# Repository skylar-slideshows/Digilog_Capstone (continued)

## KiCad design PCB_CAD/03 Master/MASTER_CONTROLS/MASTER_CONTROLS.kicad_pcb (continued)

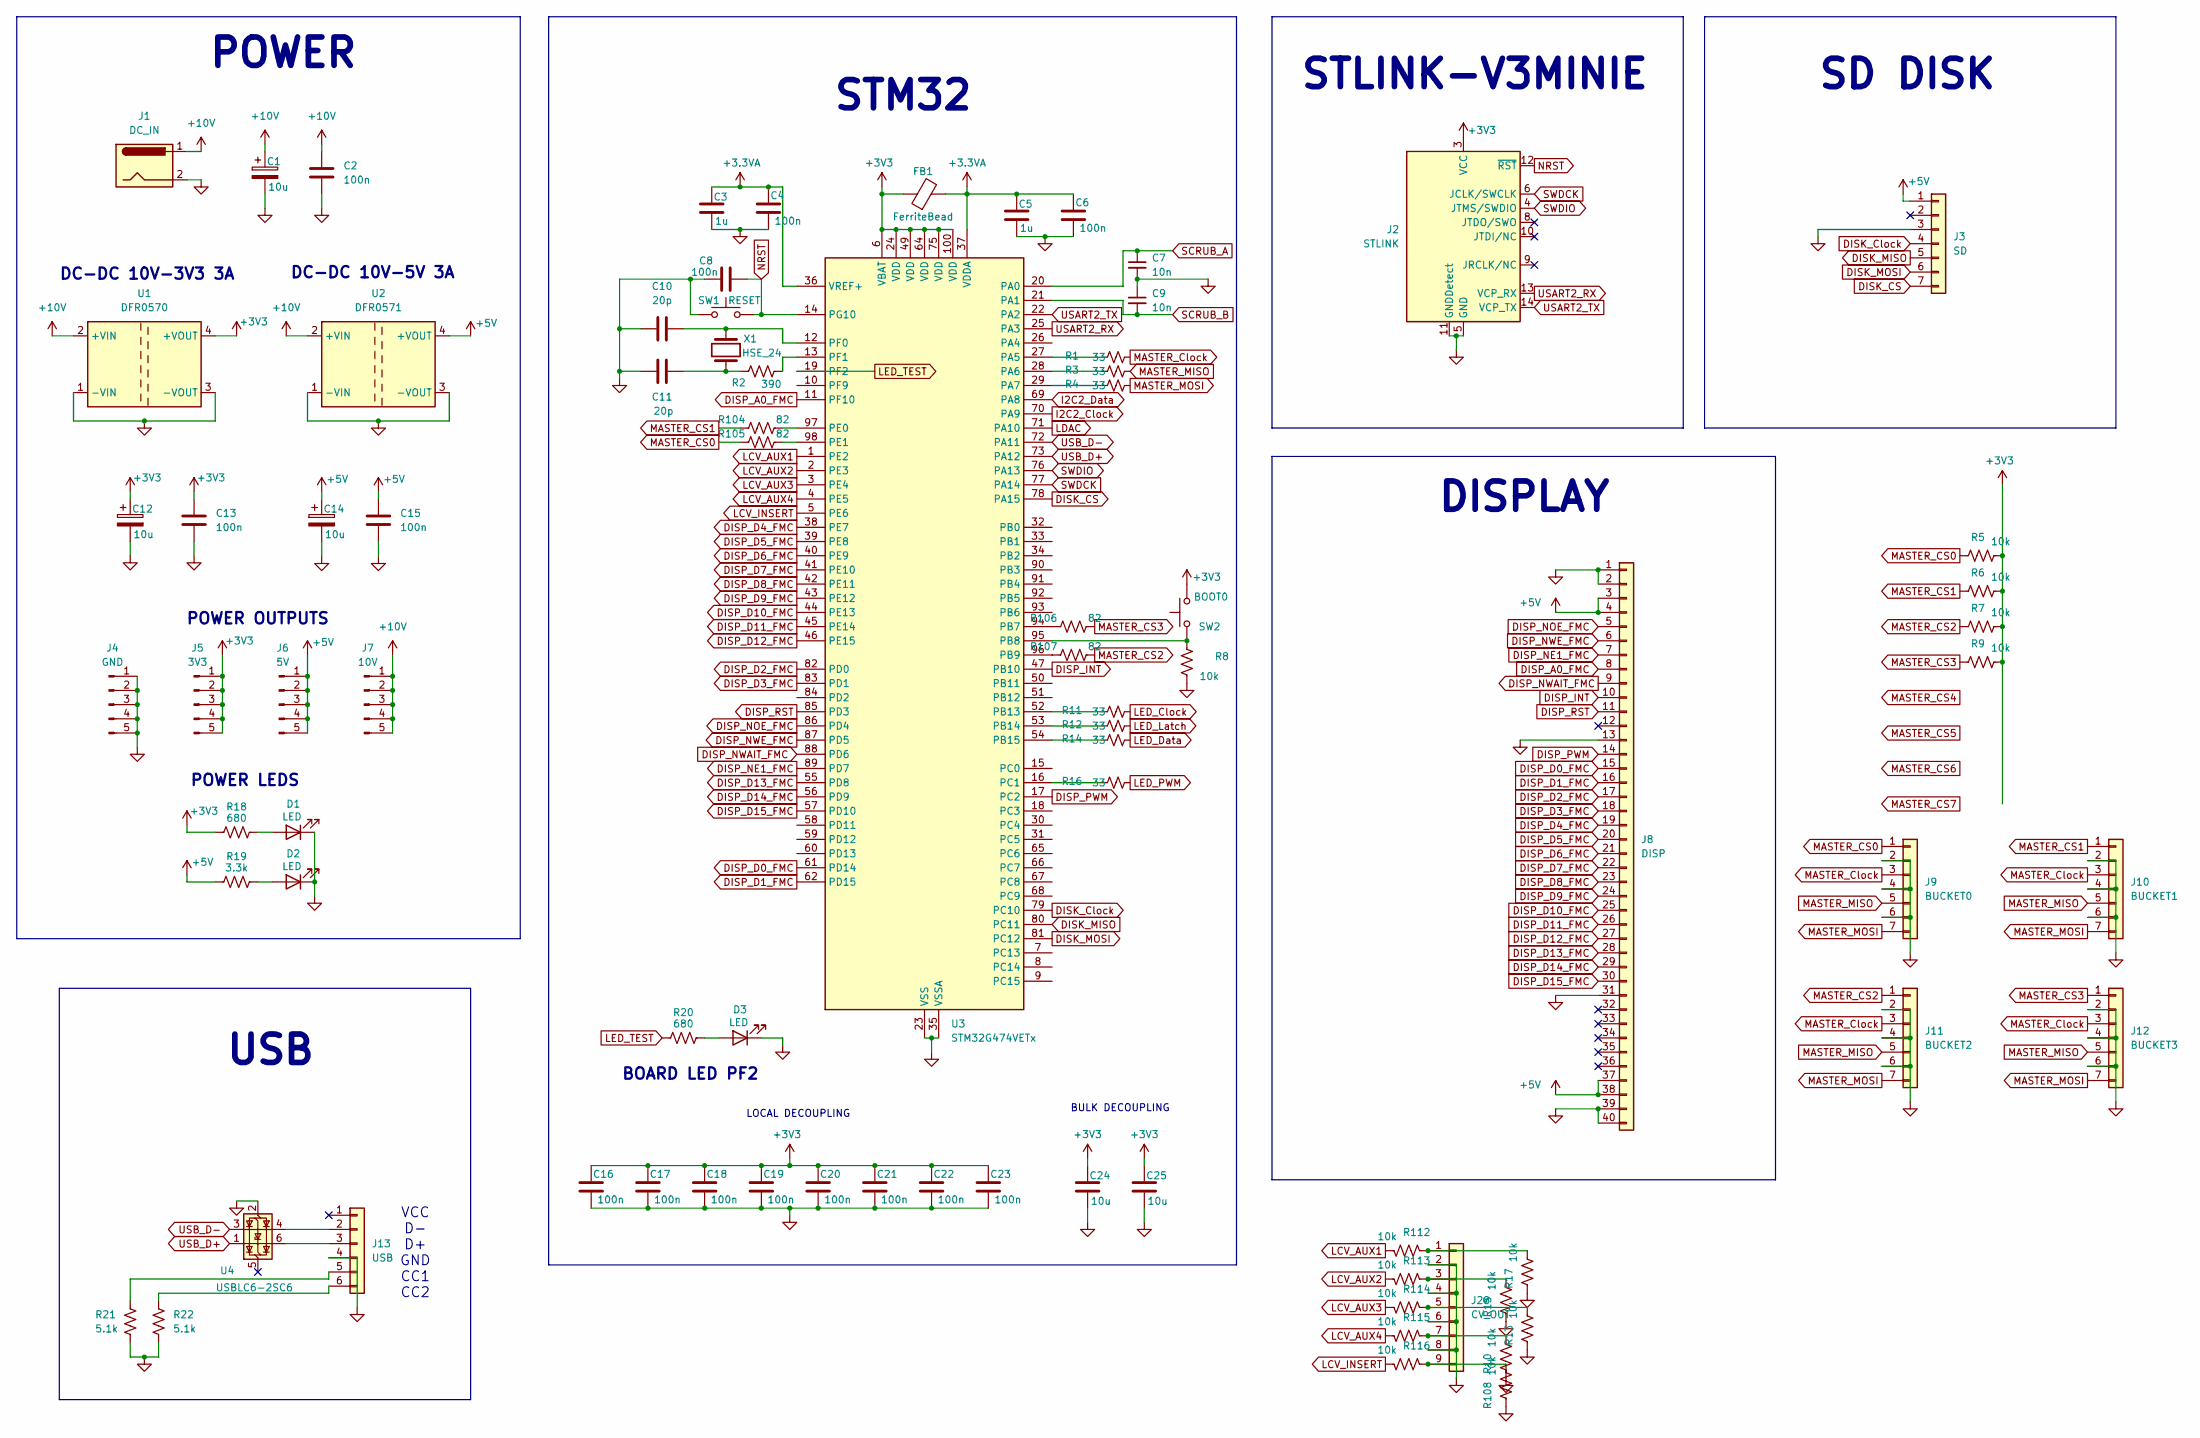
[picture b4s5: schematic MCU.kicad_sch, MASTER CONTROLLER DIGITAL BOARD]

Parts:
C1, C12, C14, C24, C25: 10u; C_1206_3216Metric; LCSC C1849
C2, C4, C6, C8, C13, C15, C16, C17, C18, C19, C20, C21, C22, C23: 100n; C_0603_1608Metric; LCSC C1590
C3, C5: 1u; C_0603_1608Metric; LCSC C15849
C7, C9: 10n; C_0402_1005Metric; LCSC C1524
C10, C11: 20p; C_0603_1608Metric; LCSC C1648
D1, D2, D3: LED; LED_0603_1608Metric; LCSC C12065
FB1: FerriteBead; Ferrite_0603_1608Metric; LCSC C1002
J1: DC_IN; BarrelJack_Horizontal; LCSC DNP
J2: STLINK; FTSH-107-01-L-DV-K-TR; LCSC C5307809
J3: SD; PinHeader_1x07_P2.54mm_Vertical; LCSC DNP
J4: GND; PinSocket_1x05_P2.54mm_Vertical; LCSC DNP
J5: 3V3; PinSocket_1x05_P2.54mm_Vertical; LCSC DNP
J6: 5V; PinSocket_1x05_P2.54mm_Vertical; LCSC DNP
J7: 10V; PinSocket_1x05_P2.54mm_Vertical; LCSC DNP
J8: DISP; GCT_FFC3B07-40-T; LCSC DNP
J9: BUCKET0; PinHeader_1x07_P2.54mm_Vertical; LCSC DNP
J10: BUCKET1; PinHeader_1x07_P2.54mm_Vertical; LCSC DNP
J11: BUCKET2; PinHeader_1x07_P2.54mm_Vertical; LCSC DNP
J12: BUCKET3; PinHeader_1x07_P2.54mm_Vertical; LCSC DNP
J13: USB; PinHeader_1x06_P2.00mm_Vertical; Part Number 1-0601FBV0T; LCSC dnp
J28: CV_OUT; PinHeader_1x09_P2.54mm_Vertical; LCSC DNP
R1, R3, R4, R11, R12, R14, R16: 33; R_0603_1608Metric; LCSC C23140
R2: 390; R_1206_3216Metric; LCSC C4491
R5, R6, R7, R8, R9, R10, R13, R15, R17, R108: 10k; R_0603_1608Metric; LCSC C25804
R18, R20: 680; R_0603_1608Metric; LCSC C23228
R19: 3.3k; R_0603_1608Metric; LCSC C22978
R21, R22: 5.1k; R_0603_1608Metric; LCSC C14677
R104, R105, R106, R107: 82; R_0603_1608Metric; LCSC C23255
R112, R113, R114, R115, R116: 10k; R_0603_1608Metric; LCSC C21190
SW1: RESET; SW_Push_1P1T_NO_CK_KMR2; LCSC C72443
SW2: BOOT0; SW_Push_1P1T_NO_CK_KMR2; LCSC C72443
U1: DFR0570; DFR05xx_DC-DC; LCSC DNP
U2: DFR0571; DFR05xx_DC-DC; LCSC DNP
U3: STM32G474VETx; LQFP-100_14x14mm_P0.5mm; LCSC C2970837
U4: USBLC6-2SC6; SOT-23-6; LCSC C7519
X1: HSE_24; Crystal_SMD_HC49-SD; LCSC C2253

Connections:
+3.3VA: C3.1, C4.1, C5.1, C6.1, FB1.2, U3.36 (VREF+), U3.37 (VDDA)
+3V3: C12.1, C13.1, C16.1, C17.1, C18.1, C19.1, C20.1, C21.1, C22.1, C23.1, C24.1, C25.1, FB1.1, J2.3 (VCC), J5.1, J5.2, J5.3, J5.4, J5.5, R5.2, R6.2, R7.2, R9.2, R18.1, SW2.2, U1.4 (+VOUT), U3.6 (VBAT), U3.24 (VDD), U3.49 (VDD), U3.64 (VDD), U3.75 (VDD), U3.100 (VDD); also elsewhere on the board
+5V: C14.1, C15.1, J3.1, J6.1, J6.2, J6.3, J6.4, J6.5, J8.3, J8.4, J8.37, J8.38, R19.1, U2.4 (+VOUT); also elsewhere on the board
+10V: C1.1, C2.1, J1.1, J7.1, J7.2, J7.3, J7.4, J7.5, U1.2 (+VIN), U2.2 (+VIN)
DISK_CS: J3.7, U3.78 (PA15)
DISK_Clock: J3.4, U3.79 (PC10)
DISK_MISO: J3.5, U3.80 (PC11)
DISK_MOSI: J3.6, U3.81 (PC12)
DISP_A0_FMC: J8.8, U3.11 (PF10)
DISP_D0_FMC: J8.15, U3.61 (PD14)
DISP_D1_FMC: J8.16, U3.62 (PD15)
DISP_D2_FMC: J8.17, U3.82 (PD0)
DISP_D3_FMC: J8.18, U3.83 (PD1)
DISP_D4_FMC: J8.19, U3.38 (PE7)
DISP_D5_FMC: J8.20, U3.39 (PE8)
DISP_D6_FMC: J8.21, U3.40 (PE9)
DISP_D7_FMC: J8.22, U3.41 (PE10)
DISP_D8_FMC: J8.23, U3.42 (PE11)
DISP_D9_FMC: J8.24, U3.43 (PE12)
DISP_D10_FMC: J8.25, U3.44 (PE13)
DISP_D11_FMC: J8.26, U3.45 (PE14)
DISP_D12_FMC: J8.27, U3.46 (PE15)
DISP_D13_FMC: J8.28, U3.55 (PD8)
DISP_D14_FMC: J8.29, U3.56 (PD9)
DISP_D15_FMC: J8.30, U3.57 (PD10)
DISP_INT: J8.10, U3.47 (PB10)
DISP_NE1_FMC: J8.7, U3.89 (PD7)
DISP_NOE_FMC: J8.5, U3.86 (PD4)
DISP_NWAIT_FMC: J8.9, U3.88 (PD6)
DISP_NWE_FMC: J8.6, U3.87 (PD5)
DISP_PWM: J8.14, U3.17 (PC2)
DISP_RST: J8.11, U3.85 (PD3)
GND: C1.2, C2.2, C3.2, C4.2, C5.2, C6.2, C7.2, C8.1, C9.1, C10.2, C11.1, C12.2, C13.2, C14.2, C15.2, C16.2, C17.2, C18.2, C19.2, C20.2, C21.2, C22.2, C23.2, C24.2, C25.2, D1.1 (K), D2.1 (K), D3.1 (K), J1.2, J2.5 (GND), J2.7 (GND), J2.11 (GNDDetect), J3.3, J4.1, J4.2, J4.3, J4.4, J4.5, J8.1, J8.2, J8.13, J8.31, J8.39, J8.40, J9.2, J9.4, J9.6, J10.2, J10.4, J10.6, J11.2, J11.4, J11.6, J12.2, J12.4, J12.6, J13.4, J28.2, J28.4, J28.6, J28.8, R8.1, R10.1, R13.1, R15.1, R17.1, R21.1, R22.1, R108.1, SW1.1, U1.1 (-VIN), U1.3 (-VOUT), U2.1 (-VIN), U2.3 (-VOUT), U3.23 (VSS), U3.35 (VSSA), U3.48 (VSS), U3.63 (VSS), U3.74 (VSS), U3.99 (VSS), U4.2 (GND); also elsewhere on the board
I2C2_Clock: U3.70 (PA9); also elsewhere on the board
I2C2_Data: U3.69 (PA8); also elsewhere on the board
LCV_AUX1: R112.2, U3.1 (PE2)
LCV_AUX2: R113.2, U3.2 (PE3)
LCV_AUX3: R114.2, U3.3 (PE4)
LCV_AUX4: R115.2, U3.4 (PE5)
LCV_INSERT: R116.2, U3.5 (PE6)
LDAC: U3.71 (PA10); also elsewhere on the board
LED_Clock: R11.2; also elsewhere on the board
LED_Data: R14.2; also elsewhere on the board
LED_Latch: R12.2; also elsewhere on the board
LED_PWM: R16.2; also elsewhere on the board
LED_TEST: R20.1, U3.19 (PF2)
MASTER_CS0: J9.1, R5.1, R105.1
MASTER_CS1: J10.1, R6.1, R104.1
MASTER_CS2: J11.1, R7.1, R107.2
MASTER_CS3: J12.1, R9.1, R106.2
MASTER_Clock: J9.3, J10.3, J11.3, J12.3, R1.2
MASTER_MISO: J9.5, J10.5, J11.5, J12.5, R3.2
MASTER_MOSI: J9.7, J10.7, J11.7, J12.7, R4.2
NRST: C8.2, J2.12 (~RST), SW1.2, U3.14 (PG10)
unnamed: C11.2, R2.1, X1.2
unnamed: D1.2 (A), R18.2
unnamed: D2.2 (A), R19.2
unnamed: D3.2 (A), R20.2
unnamed: J13.2, U4.4 (I/O2)
unnamed: J13.3, U4.6 (I/O1)
unnamed: J13.5, R21.2
unnamed: J13.6, R22.2
unnamed: J28.1, R17.2, R112.1
unnamed: J28.3, R15.2, R113.1
unnamed: J28.5, R13.2, R114.1
unnamed: J28.7, R10.2, R115.1
unnamed: J28.9, R108.2, R116.1
unnamed: R1.1, U3.27 (PA5)
unnamed: R3.1, U3.28 (PA6)
unnamed: R4.1, U3.29 (PA7)
unnamed: R106.1, U3.94 (PB7)
unnamed: R8.2, SW2.1, U3.95 (PB8)
unnamed: R107.1, U3.96 (PB9)
unnamed: R11.1, U3.52 (PB13)
unnamed: R12.1, U3.53 (PB14)
unnamed: R14.1, U3.54 (PB15)
unnamed: R16.1, U3.16 (PC1)
unnamed: R104.2, U3.97 (PE0)
unnamed: R105.2, U3.98 (PE1)
unnamed: C10.1, U3.12 (PF0), X1.1
unnamed: R2.2, U3.13 (PF1)
SCRUB_A: C7.1, U3.20 (PA0); also elsewhere on the board
SCRUB_B: C9.2, U3.21 (PA1); also elsewhere on the board
SWDCK: J2.6 (JCLK/SWCLK), U3.77 (PA14)
SWDIO: J2.4 (JTMS/SWDIO), U3.76 (PA13)
USART2_RX: J2.13 (VCP_RX), U3.25 (PA3)
USART2_TX: J2.14 (VCP_TX), U3.22 (PA2)
USB_D+: U3.73 (PA12), U4.1 (I/O1)
USB_D-: U3.72 (PA11), U4.3 (I/O2)

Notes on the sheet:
DISPLAY
POWER LEDS
STLINK-V3MINIE
STM32
DC-DC 10V-5V 3A
BULK DECOUPLING
LOCAL DECOUPLING
POWER
BOARD LED PF2
POWER OUTPUTS
DC-DC 10V-3V3 3A
SD DISK
USB
VCC D- D+ GND CC1 CC2

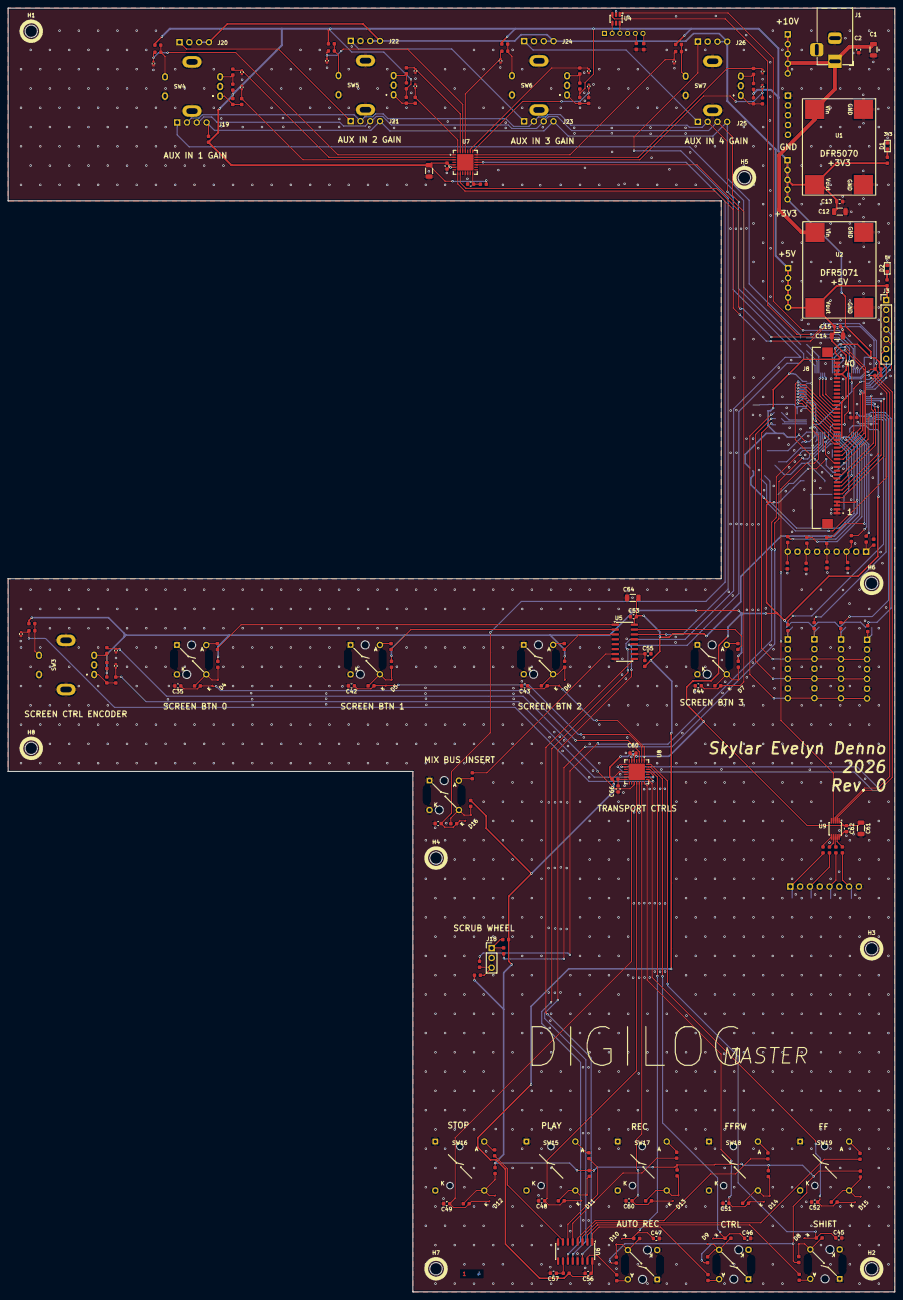
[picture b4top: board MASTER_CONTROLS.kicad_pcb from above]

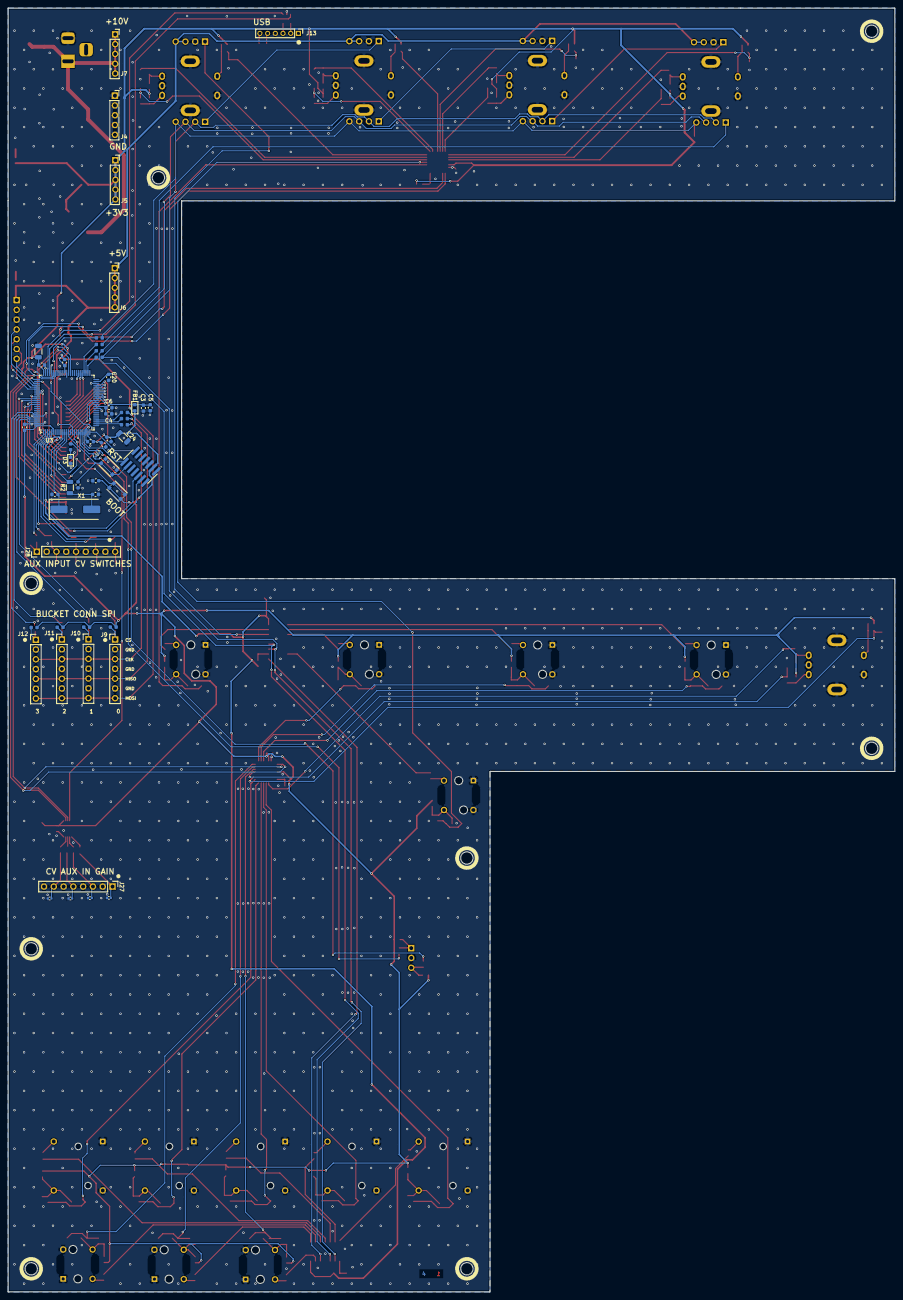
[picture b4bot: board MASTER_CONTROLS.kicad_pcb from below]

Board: 4 copper layers, 230.0 x 333.0 mm, 264 parts (54 on the bottom side), 190 nets.

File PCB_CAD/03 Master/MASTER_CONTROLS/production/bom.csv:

Designator,Footprint,Quantity,Value,LCSC Part #
"C1, C12, C14, C24, C25, C54, C59, C61",1206,8,10u,C1849
"C10, C11",0603,2,20p,C1648
"C13, C15, C16, C17, C18, C19, C2, C20, C21, C22, C23, C4, C53, C55, C56, C57, C58, C6, C60, C62, C65, C66, C8",0603,23,100n,C1590
"C26, C27, C28, C29, C30, C31, C32, C33, C34, C36, C37, C38, C39, C40, C41, C63, C64, C67, C68, C7, C9",0402,21,10n,C1524
"C3, C35, C42, C43, C44, C45, C46, C47, C48, C49, C5, C50, C51, C52, C69",0603,15,1u,C15849
"D1, D2, D3",0603,3,LED,C12065
"D10, D11, D12, D13, D14, D15, D16, D4, D5, D6, D7, D8, D9",D_SOD-323,13,1N4148,C2128
FB1,Ferrite_0603_1608Metric,1,FerriteBead,C1002
J1,BarrelJack_Horizontal,1,DC_IN,DNP
J10,PinHeader_1x07_P2.54mm_Vertical,1,BUCKET1,DNP
J11,PinHeader_1x07_P2.54mm_Vertical,1,BUCKET2,DNP
J12,PinHeader_1x07_P2.54mm_Vertical,1,BUCKET3,DNP
J13,PinHeader_1x06_P2.00mm_Vertical,1,USB,dnp
J18,PinHeader_1x03_P2.54mm_Vertical,1,SCRUB_ENCODER,DNP
"J19, J21, J23, J25",PinSocket_1x04_P2.54mm_Vertical,4,Data,DNP
J2,FTSH-107-01-L-DV-K-TR,1,STLINK,C5307809
"J20, J22, J24, J26",PinSocket_1x04_P2.54mm_Vertical,4,Pow,DNP
J27,PinHeader_1x08_P2.54mm_Vertical,1,CV_OUT,DNP
J28,PinHeader_1x09_P2.54mm_Vertical,1,CV_OUT,DNP
J3,PinHeader_1x07_P2.54mm_Vertical,1,SD,DNP
J4,PinSocket_1x05_P2.54mm_Vertical,1,GND,DNP
J5,PinSocket_1x05_P2.54mm_Vertical,1,3V3,DNP
J6,PinSocket_1x05_P2.54mm_Vertical,1,5V,DNP
J7,PinSocket_1x05_P2.54mm_Vertical,1,10V,DNP
J8,GCT_FFC3B07-40-T,1,DISP,DNP
J9,PinHeader_1x07_P2.54mm_Vertical,1,BUCKET0,DNP
"R1, R11, R12, R14, R16, R3, R4",0603,7,33,C23140
"R10, R100, R108, R13, R15, R17, R23, R24, R25, R26, R27, R28, R29, R30, R31, R43, R44, R45, R46, R47, R48, R5, R6, R7, R75, R8, R81, R9, R93, R94, R95, R99",0603,32,10k,C25804
"R101, R102, R103, R96",0603,4,470,C23179
"R104, R105, R106, R107",0603,4,82,C23255
"R109, R41, R42, R59, R60, R63, R64, R65, R76, R77, R78, R79, R80",0603,13,47k,C25819
"R110, R57, R58, R66, R67, R71, R72, R73, R88, R89, R90, R91, R92",0603,13,470,C25241
"R111, R49, R52, R61, R62, R68, R69, R70, R74, R82, R83, R84, R85, R86, R87",0603,15,15k,C22809
"R112, R113, R114, R115, R116",0603,5,10k,C21190
"R18, R20",0603,2,680,C23228
R19,0603,1,3.3k,C22978
R2,1206,1,390,C4491
"R21, R22",0603,2,5.1k,C14677
"R32, R33, R34, R35, R36, R37, R38, R39, R40, R50, R51, R53, R54, R55, R56",0603,15,1k,C21190
"R97, R98",0603,2,1.5k,C22843
SW1,SW_Push_1P1T_NO_CK_KMR2,1,RESET,C72443
SW10,CFPB-1CC-4W6_LOWPROF,1,B2,DNP
SW11,CFPB-1CC-4W6_LOWPROF,1,B3,DNP
SW12,CFPB-1CC-4W6_LOWPROF,1,B4,DNP
"SW13, SW14",CFPB-1CC-4W6_LOWPROF,2,B5,DNP
SW15,CFPB-1CC-4W2,1,B_PLAY,DNP
SW16,CFPB-1CC-4W2,1,B_STOP,DNP
SW17,CFPB-1CC-4W2,1,B_REC,DNP
SW18,CFPB-1CC-4W2,1,B_FRW,DNP
SW19,CFPB-1CC-4W2,1,B_FF,DNP
SW2,SW_Push_1P1T_NO_CK_KMR2,1,BOOT0,C72443
SW20,CFPB-1CC-4W6_LOWPROF,1,INSERT,DNP
SW3,EC11J0924411,1,K4,DNP
SW4,EC11J0924411,1,K0,DNP
SW5,EC11J0924411,1,K1,DNP
SW6,EC11J0924411,1,K2,DNP
SW7,EC11J0924411,1,K3,DNP
SW8,CFPB-1CC-4W6_LOWPROF,1,B0,DNP
SW9,CFPB-1CC-4W6_LOWPROF,1,B1,DNP
U1,DFR05xx_DC-DC,1,DFR0570,DNP
U2,DFR05xx_DC-DC,1,DFR0571,DNP
U3,LQFP-100_14x14mm_P0.5mm,1,STM32G474VETx,C2970837
U4,SOT-23-6,1,USBLC6-2SC6,C7519
"U5, U6",SOIC-16_3.9x9.9mm_P1.27mm,2,74HCT595,C282339
U7,QFN-28-1EP_6x6mm_P0.65mm_EP4.25x4.25mm,1,MCP23017_0,C629439
U8,QFN-28-1EP_6x6mm_P0.65mm_EP4.25x4.25mm,1,MCP23017_1,C629439
U9,MSOP-10_3x3mm_P0.5mm,1,MCP4728,C108207
X1,Crystal_SMD_HC49-SD,1,HSE_24,C2253

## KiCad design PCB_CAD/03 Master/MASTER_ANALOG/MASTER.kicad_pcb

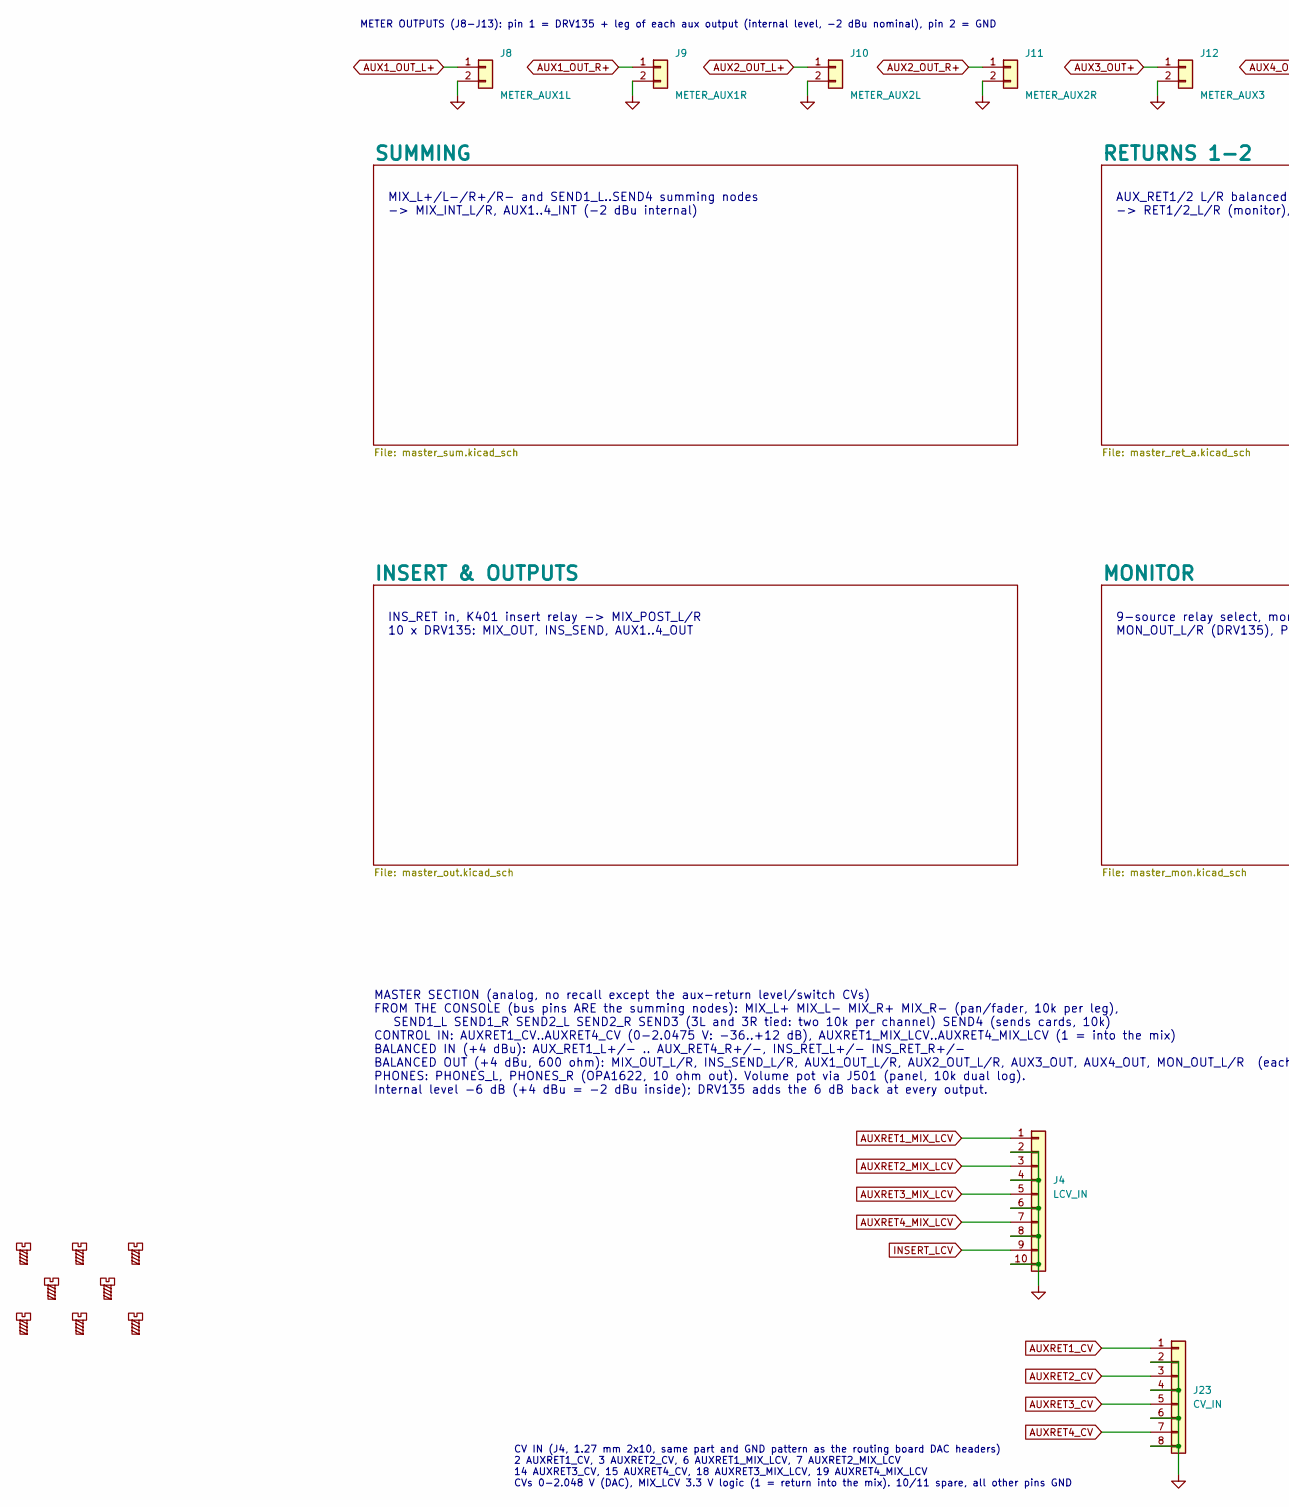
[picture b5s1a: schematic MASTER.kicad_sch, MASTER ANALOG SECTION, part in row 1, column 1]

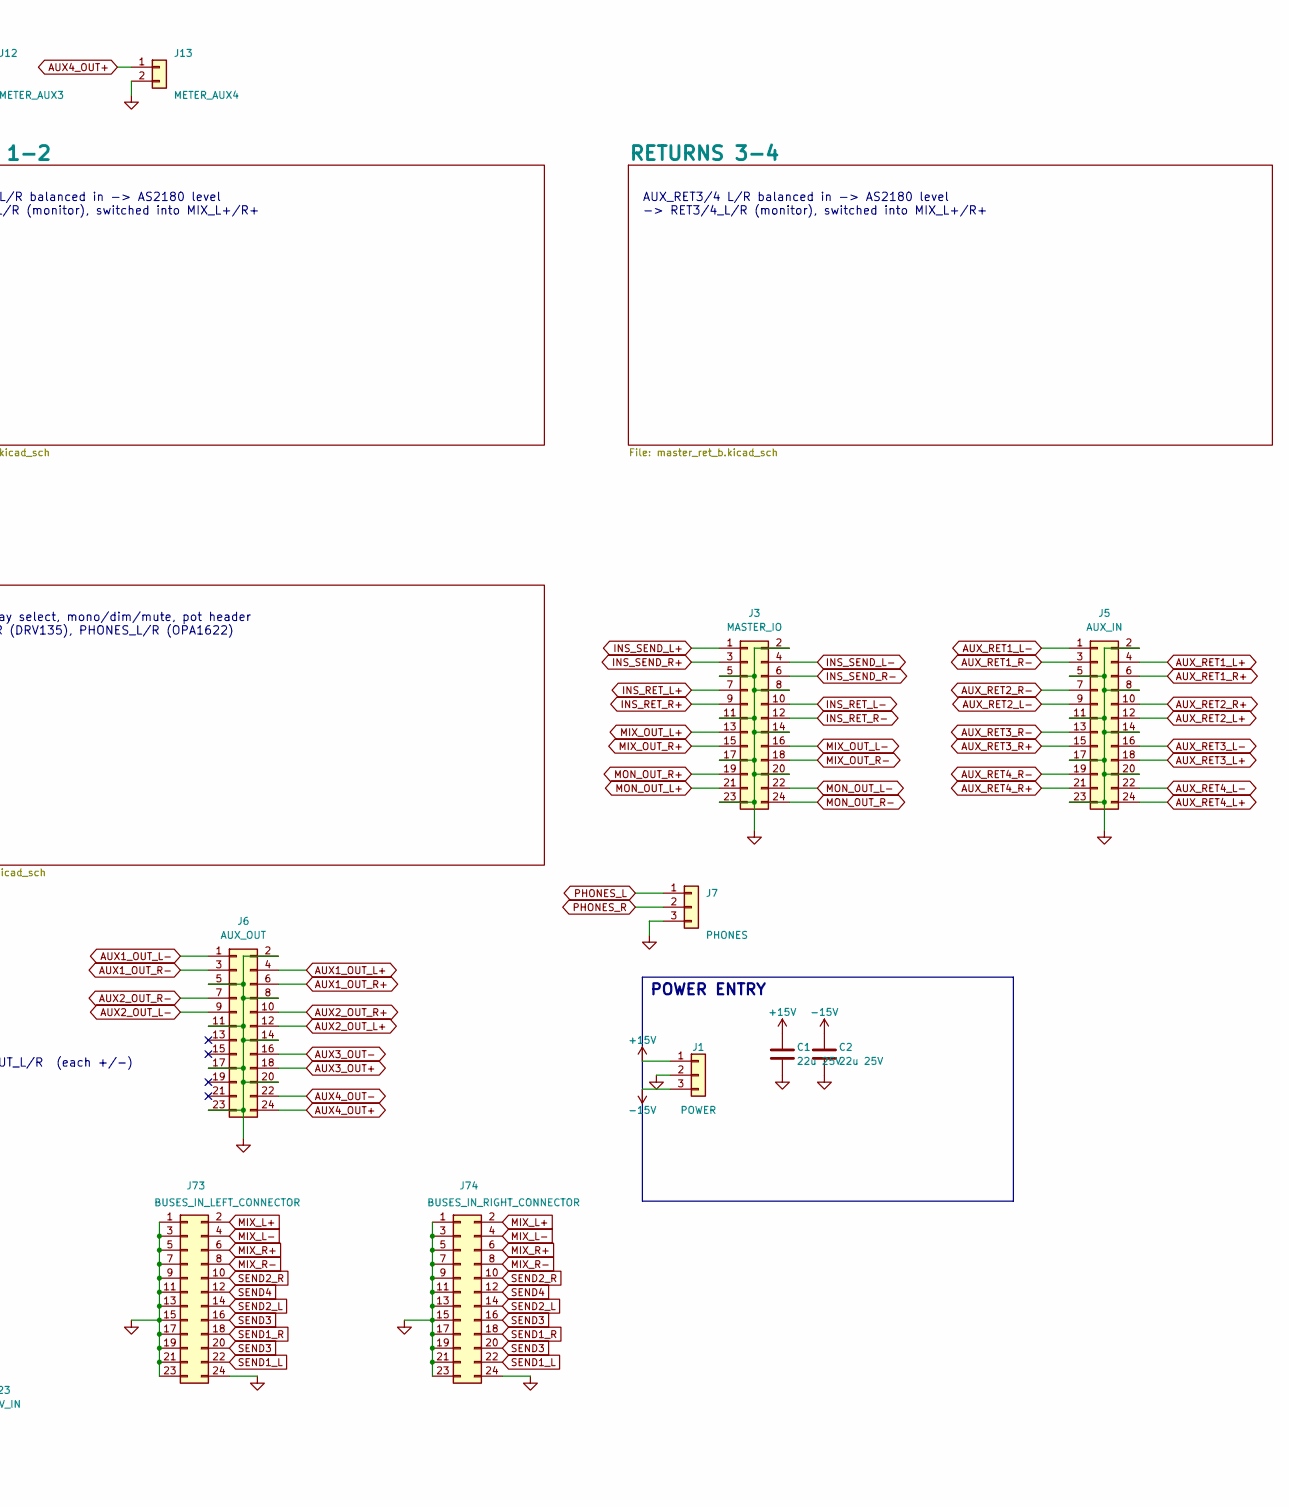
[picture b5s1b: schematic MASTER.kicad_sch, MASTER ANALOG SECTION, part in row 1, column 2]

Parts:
C1, C2: 22u 25V; C_1210_3225Metric; LCSC C21397
H1, H2, H3, H4, H5, H6, H7, H8: MountingScrew; MountingHole_3.2mm_M3; LCSC dnp
J1: POWER; Samtec_HPM-03-05-x-S_Straight_1x03_Pitch5.08mm; LCSC dnp
J3: MASTER_IO; IDC-Header_2x12_P2.54mm_Vertical; LCSC C53207829
J4: LCV_IN; PinHeader_1x10_P2.54mm_Vertical; LCSC dnp
J5: AUX_IN; IDC-Header_2x12_P2.54mm_Vertical; LCSC C53207829
J6: AUX_OUT; IDC-Header_2x12_P2.54mm_Vertical; LCSC C53207829
J7: PHONES; PinHeader_1x03_P2.54mm_Vertical; LCSC dnp
J8: METER_AUX1L; PinHeader_1x02_P2.54mm_Vertical; LCSC dnp
J9: METER_AUX1R; PinHeader_1x02_P2.54mm_Vertical; LCSC dnp
J10: METER_AUX2L; PinHeader_1x02_P2.54mm_Vertical; LCSC dnp
J11: METER_AUX2R; PinHeader_1x02_P2.54mm_Vertical; LCSC dnp
J12: METER_AUX3; PinHeader_1x02_P2.54mm_Vertical; LCSC dnp
J13: METER_AUX4; PinHeader_1x02_P2.54mm_Vertical; LCSC dnp
J23: CV_IN; PinHeader_1x08_P2.54mm_Vertical; LCSC dnp
J73: BUSES_IN_LEFT_CONNECTOR; IDC-Header_2x12_P2.54mm_Vertical; LCSC C53207829
J74: BUSES_IN_RIGHT_CONNECTOR; IDC-Header_2x12_P2.54mm_Vertical; LCSC C53207829

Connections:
+15V: C1.1, J1.1; also elsewhere on the board
-15V: C2.1, J1.3; also elsewhere on the board
AUX1_OUT_L+: J6.4, J8.1; also elsewhere on the board
AUX1_OUT_L-: J6.1; also elsewhere on the board
AUX1_OUT_R+: J6.6, J9.1; also elsewhere on the board
AUX1_OUT_R-: J6.3; also elsewhere on the board
AUX2_OUT_L+: J6.12, J10.1; also elsewhere on the board
AUX2_OUT_L-: J6.9; also elsewhere on the board
AUX2_OUT_R+: J6.10, J11.1; also elsewhere on the board
AUX2_OUT_R-: J6.7; also elsewhere on the board
AUX3_OUT+: J6.18, J12.1; also elsewhere on the board
AUX3_OUT-: J6.16; also elsewhere on the board
AUX4_OUT+: J6.24, J13.1; also elsewhere on the board
AUX4_OUT-: J6.22; also elsewhere on the board
AUXRET1_CV: J23.1; also elsewhere on the board
AUXRET1_MIX_LCV: J4.1; also elsewhere on the board
AUXRET2_CV: J23.3; also elsewhere on the board
AUXRET2_MIX_LCV: J4.3; also elsewhere on the board
AUXRET3_CV: J23.5; also elsewhere on the board
AUXRET3_MIX_LCV: J4.5; also elsewhere on the board
AUXRET4_CV: J23.7; also elsewhere on the board
AUXRET4_MIX_LCV: J4.7; also elsewhere on the board
AUX_RET1_L+: J5.4; also elsewhere on the board
AUX_RET1_L-: J5.1; also elsewhere on the board
AUX_RET1_R+: J5.6; also elsewhere on the board
AUX_RET1_R-: J5.3; also elsewhere on the board
AUX_RET2_L+: J5.12; also elsewhere on the board
AUX_RET2_L-: J5.9; also elsewhere on the board
AUX_RET2_R+: J5.10; also elsewhere on the board
AUX_RET2_R-: J5.7; also elsewhere on the board
AUX_RET3_L+: J5.18; also elsewhere on the board
AUX_RET3_L-: J5.16; also elsewhere on the board
AUX_RET3_R+: J5.15; also elsewhere on the board
AUX_RET3_R-: J5.13; also elsewhere on the board
AUX_RET4_L+: J5.24; also elsewhere on the board
AUX_RET4_L-: J5.22; also elsewhere on the board
AUX_RET4_R+: J5.21; also elsewhere on the board
AUX_RET4_R-: J5.19; also elsewhere on the board
GND: C1.2, C2.2, J1.2, J3.2, J3.5, J3.8, J3.11, J3.14, J3.17, J3.20, J3.23, J4.2, J4.4, J4.6, J4.8, J4.10, J5.2, J5.5, J5.8, J5.11, J5.14, J5.17, J5.20, J5.23, J6.2, J6.5, J6.8, J6.11, J6.14, J6.17, J6.20, J6.23, J7.3, J8.2, J9.2, J10.2, J11.2, J12.2, J13.2, J23.2, J23.4, J23.6, J23.8, J73.1, J73.3, J73.5, J73.7, J73.9, J73.11, J73.13, J73.15, J73.17, J73.19, J73.21, J73.23, J73.24, J74.1, J74.3, J74.5, J74.7, J74.9, J74.11, J74.13, J74.15, J74.17, J74.19, J74.21, J74.23, J74.24; also elsewhere on the board
INSERT_LCV: J4.9; also elsewhere on the board
INS_RET_L+: J3.7; also elsewhere on the board
INS_RET_L-: J3.10; also elsewhere on the board
INS_RET_R+: J3.9; also elsewhere on the board
INS_RET_R-: J3.12; also elsewhere on the board
INS_SEND_L+: J3.1; also elsewhere on the board
INS_SEND_L-: J3.4; also elsewhere on the board
INS_SEND_R+: J3.3; also elsewhere on the board
INS_SEND_R-: J3.6; also elsewhere on the board
MIX_L+: J73.2, J74.2; also elsewhere on the board
MIX_L-: J73.4, J74.4; also elsewhere on the board
MIX_OUT_L+: J3.13; also elsewhere on the board
MIX_OUT_L-: J3.16; also elsewhere on the board
MIX_OUT_R+: J3.15; also elsewhere on the board
MIX_OUT_R-: J3.18; also elsewhere on the board
MIX_R+: J73.6, J74.6; also elsewhere on the board
MIX_R-: J73.8, J74.8; also elsewhere on the board
MON_OUT_L+: J3.21; also elsewhere on the board
MON_OUT_L-: J3.22; also elsewhere on the board
MON_OUT_R+: J3.19; also elsewhere on the board
MON_OUT_R-: J3.24; also elsewhere on the board
PHONES_L: J7.1; also elsewhere on the board
PHONES_R: J7.2; also elsewhere on the board
SEND1_L: J73.22, J74.22; also elsewhere on the board
SEND1_R: J73.18, J74.18; also elsewhere on the board
SEND2_L: J73.14, J74.14; also elsewhere on the board
SEND2_R: J73.10, J74.10; also elsewhere on the board
SEND3: J73.16, J73.20, J74.16, J74.20; also elsewhere on the board
SEND4: J73.12, J74.12; also elsewhere on the board

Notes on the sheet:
MASTER SECTION (analog, no recall except the aux-return level/switch CVs) FROM THE CONSOLE (bus pins ARE the summing nodes): MIX_L+ MIX_L- MIX_R+ MIX_R- (pan/fader, 10k per leg), SEND1_L SEND1_R SEND2_L SEND2_R SEND3 (3L and 3R tied: two 10k per channel) SEND4 (sends cards, 10k) CONTROL IN: AUXRET1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
AUX_RET1/2 L/R balanced in -> AS2180 level -> RET1/2_L/R (monitor), switched into MIX_L+/R+
POWER ENTRY
CV IN (J4, 1.27 mm 2x10, same part and GND pattern as the routing board DAC headers) 2 AUXRET1_CV, 3 AUXRET2_CV, 6 AUXRET1_MIX_LCV, 7 AUXRET2_MIX_LCV 14 AUXRET3_CV, 15 AUXRET4_CV, 18 AUXRET3_MIX_LCV, 19 AUXRET4_MIX_LCV CVs 0-2.048 V (DAC), MIX_LCV 3.3 V logic (1 = return into the mix). 10/11 spare,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
9-source relay select, mono/dim/mute, pot header MON_OUT_L/R (DRV135), PHONES_L/R (OPA1622)
METER OUTPUTS (J8-J13): pin 1 = DRV135 + leg of each aux output (internal level, -2 dBu nominal), pin 2 = GND
AUX_RET3/4 L/R balanced in -> AS2180 level -> RET3/4_L/R (monitor), switched into MIX_L+/R+
INS_RET in, K401 insert relay -> MIX_POST_L/R 10 x DRV135: MIX_OUT, INS_SEND, AUX1..4_OUT
MIX_L+/L-/R+/R- and SEND1_L..SEND4 summing nodes -> MIX_INT_L/R, AUX1..4_INT (-2 dBu internal)
